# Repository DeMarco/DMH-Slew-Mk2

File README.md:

# DMH-Slew-Mk2
Second version of my Voltage Controlled Slew Limiter in Kosmo format.

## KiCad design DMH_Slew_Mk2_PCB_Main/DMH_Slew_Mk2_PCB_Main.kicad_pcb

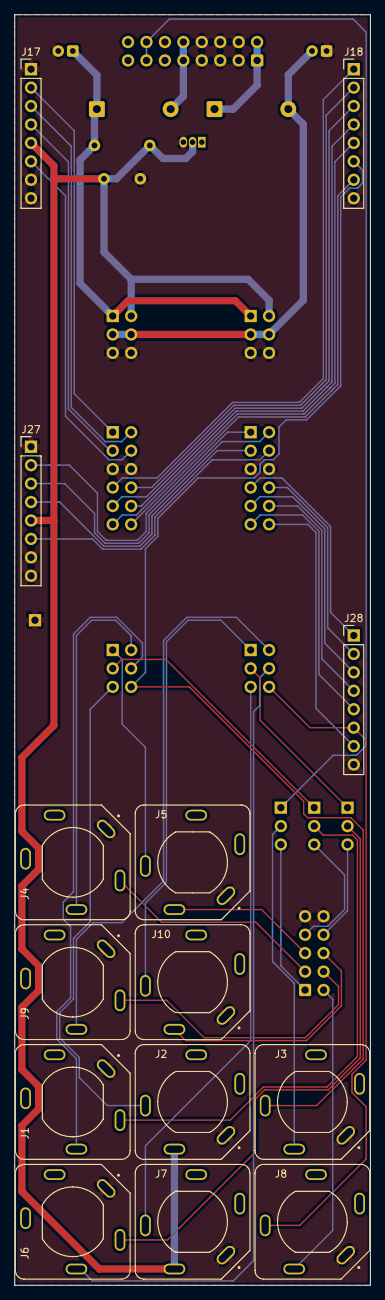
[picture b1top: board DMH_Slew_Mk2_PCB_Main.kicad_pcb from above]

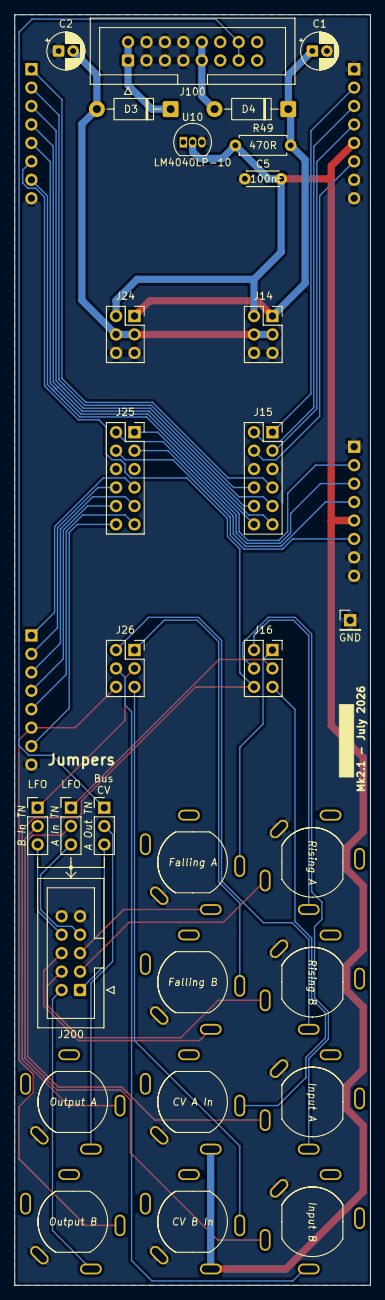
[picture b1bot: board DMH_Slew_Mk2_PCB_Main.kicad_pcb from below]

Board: 2 copper layers, 49.0 x 175.0 mm, 33 parts (19 on the bottom side), 50 nets.

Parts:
C1, C2: 47uF; CP_Radial_D5.0mm_P2.00mm
C5: 100nF; C_Disc_D4.3mm_W1.9mm_P5.00mm
D3, D4: SB140; D_DO-41_SOD81_P10.16mm_Horizontal
J0: Conn_01x01; PinHeader_1x01_P2.54mm_Vertical
J1, J2, J3, J4, J5, J6, J7, J8, J9, J10: TS_Jack_6.35mm_Sw; CUI_SJ-63083D
J14, J16, J24, J26: Conn_02x03_Top_Bottom; PinSocket_2x03_P2.54mm_Vertical
J15, J25: Conn_02x06_Top_Bottom; PinSocket_2x06_P2.54mm_Vertical
J17, J18, J27, J28: Conn_01x08; PinHeader_1x08_P2.54mm_Vertical
J100: IDC_02x08; IDC-Header_2x08_P2.54mm_Vertical_Eurorack
J200: IDC_02x05; IDC-Header_2x05_P2.54mm_Vertical_BackBone
JP1, JP2, JP3: Jumper_3_Bridged12; PinHeader_1x03_P2.54mm_Vertical
R49: 470R; R_Axial_DIN0207_L6.3mm_D2.5mm_P7.62mm_Horizontal
U10: LM4040LP-10; TO-92_Inline

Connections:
+10V: C5.1, J2.TN (2), J7.TN (2), J14.2, J17.5, J24.2, J27.5, R49.1, U10.2 (K)
+12V: C1.1, D4.1 (K), J14.1, J24.1, R49.2
-12V: C2.2, D3.2 (A), J14.3, J14.4, J24.3, J24.4
A_CV_Buff_M: J15.4, J17.6
A_CV_In_Jack_M: J2.T (3), J16.5
A_Diff_Amp_M: J15.1, J17.2
A_F_Gate_Jack_M: J5.T (3), J16.1
A_F_Gate_Jack_TN_M: J5.TN (2), J200.3
A_F_LED_M: J15.10, J18.4
A_Fall_CV_M: J15.3, J17.4
A_In_Jack_TN_M: J1.TN (2), JP2.2 (C)
A_Input_Jack_M: J1.T (3), J16.4
A_LinLog_Sw_p2_M: J15.8, J18.2
A_LinLog_Sw_p5_M: J15.7, J18.1
A_Loopback_M: J16.3, JP2.1 (A)
A_Out_Jack_M: J3.T (3), J16.6, J18.6
A_Out_Jack_TN_M: J3.TN (2), JP1.2 (C)
A_R_Gate_Jack_M: J4.T (3), J16.2
A_R_Gate_Jack_TN_M: J4.TN (2), J200.2
A_R_LED_M: J15.9, J18.3
A_Rise_CV_M: J15.2, J17.3
A_Rng_Sw_p1_M: J15.12, J18.7
A_Rng_Sw_p3_M: J15.11, J18.5
B_CV_Buff_M: J25.4, J27.6
B_CV_In_Jack_M: J7.T (3), J26.5
B_Diff_Amp_M: J25.1, J27.2
B_F_Gate_Jack_M: J10.T (3), J26.1
B_F_Gate_Jack_TN_M: J10.TN (2), J200.8
B_F_LED_M: J25.10, J28.4
B_Fall_CV_M: J25.3, J27.4
B_In_Jack_TN_M: J6.TN (2), JP3.2 (C)
B_Input_Jack_M: J6.T (3), J26.4
B_LinLog_Sw_p2_M: J25.8, J28.2
B_LinLog_Sw_p5_M: J25.7, J28.1
B_Loopback_M: J26.3, JP3.1 (A)
B_Out_Jack_M: J8.T (3), J26.6, J28.6
B_Out_Jack_TN_M: J8.TN (2), J200.6
B_R_Gate_Jack_M: J9.T (3), J26.2
B_R_Gate_Jack_TN_M: J9.TN (2), J200.7
B_R_LED_M: J25.9, J28.3
B_Rise_CV_M: J25.2, J27.3
B_Rng_Sw_p1_M: J25.12, J28.7
B_Rng_Sw_p3_M: J25.11, J28.5
Bus_CV_M: J100.7a, J100.7b, JP1.1 (A)
GND: C1.2, C2.1, C5.2, J0.1 (Pin_1_1), J1.S (1), J2.S (1), J3.S (1), J4.S (1), J5.S (1), J6.S (1), J7.S (1), J8.S (1), J9.S (1), J10.S (1), J14.5, J14.6, J15.5, J15.6, J17.1, J17.7, J17.8, J18.8, J24.5, J24.6, J25.5, J25.6, J27.1, J27.7, J27.8, J28.8, J100.2a, J100.2b, J100.3a, J100.3b, J100.4a, J100.4b, J200.5, J200.10, U10.3 (A)
unnamed: D3.1 (K), J100.1a, J100.1b
unnamed: D4.2 (A), J100.5a, J100.5b
unnamed: J200.1, JP1.3 (B)
unnamed: J200.4, JP2.3 (B)
unnamed: J200.9, JP3.3 (B)

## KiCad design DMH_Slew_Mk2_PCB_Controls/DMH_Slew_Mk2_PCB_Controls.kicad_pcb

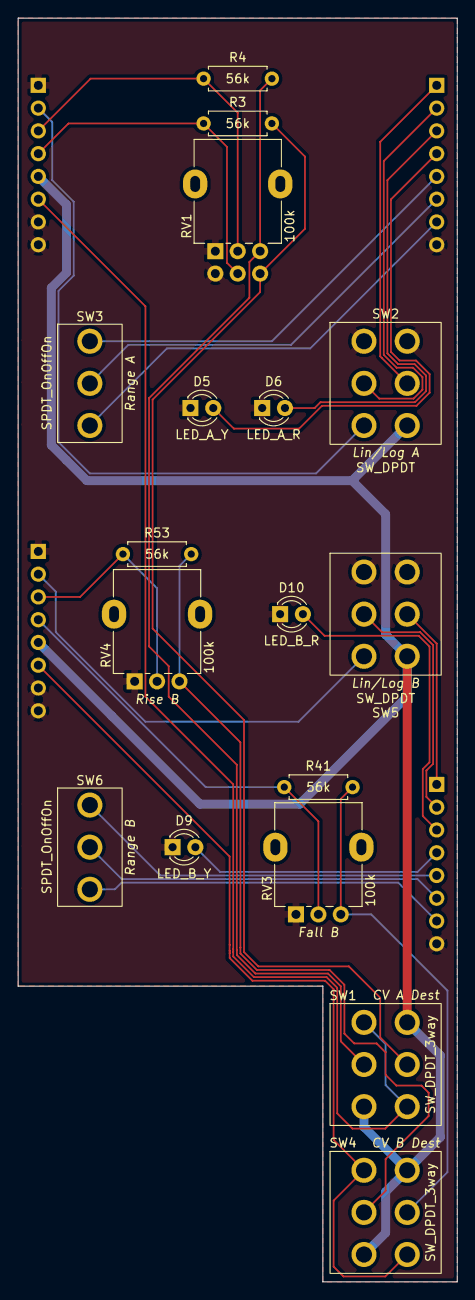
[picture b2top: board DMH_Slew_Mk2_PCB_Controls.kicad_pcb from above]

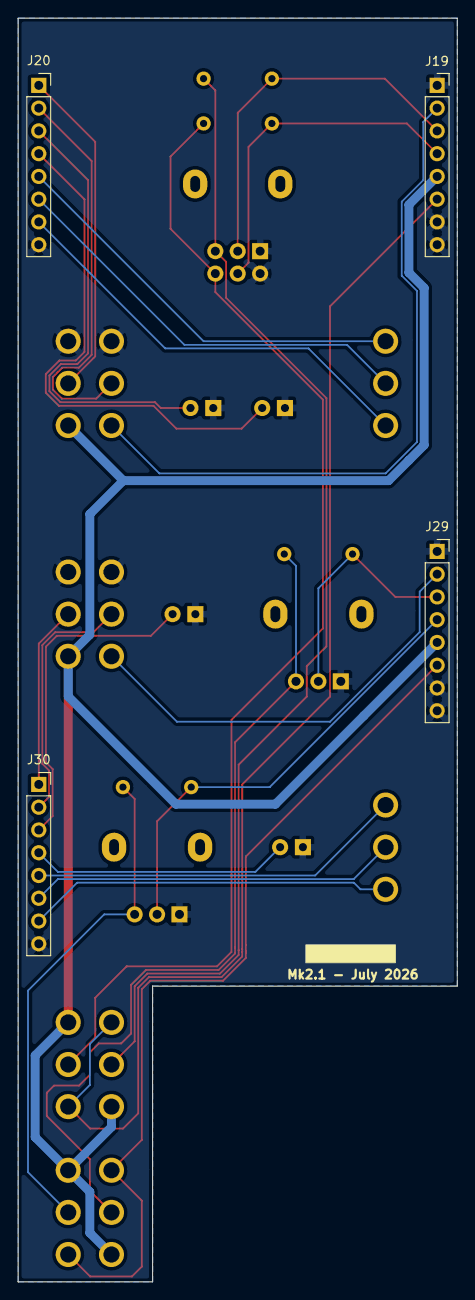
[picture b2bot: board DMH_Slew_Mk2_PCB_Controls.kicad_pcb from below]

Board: 2 copper layers, 49.0 x 141.0 mm, 21 parts (4 on the bottom side), 28 nets.

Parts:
D5: LED_A_Y; LED_D3.0mm
D6: LED_A_R; LED_D3.0mm
D9: LED_B_Y; LED_D3.0mm
D10: LED_B_R; LED_D3.0mm
J19, J20, J29, J30: Conn_01x08; PinSocket_1x08_P2.54mm_Vertical
R3, R4, R41, R53: 56k; R_Axial_DIN0207_L6.3mm_D2.5mm_P7.62mm_Horizontal
RV1: 100k; Potentiometer_Alpha_RD902F-40-00D_Dual_Vertical
RV3, RV4: 100k; Potentiometer_Alpha_RD901F-40-00D_Single_Vertical
SW1, SW4: SW_DPDT_3way; Toggle_Switch_2_Poles_TE
SW2, SW5: SW_DPDT; Toggle_Switch_2_Poles_TE
SW3, SW6: SPDT_OnOffOn; Toggle_Switch_TE

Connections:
+10V: J19.5, J29.5, SW1.1 (A), SW1.6 (C), SW2.4 (A), SW4.1 (A), SW4.6 (C), SW5.4 (A)
A_CV_Buff_C: J19.6, SW1.3 (C), SW1.4 (A)
A_Diff_Amp_C: J19.2, SW2.1 (A)
A_F_LED_C: D5.2 (A), J20.4
A_Fall_CV_C: J19.4, R3.1, RV1.5
A_LinLog_Sw_p2_C: J20.2, SW2.2 (B)
A_LinLog_Sw_p5_C: J20.1, SW2.5 (B)
A_Out_Jack_C: J20.6, SW3.2 (B)
A_R_LED_C: D6.2 (A), J20.3
A_Rise_CV_C: J19.3, R4.1, RV1.2
A_Rng_Sw_p1_C: J20.7, SW3.1 (A)
A_Rng_Sw_p3_C: J20.5, SW3.3 (C)
B_CV_Buff_C: J29.6, SW4.3 (C), SW4.4 (A)
B_Diff_Amp_C: J29.2, SW5.1 (A)
B_F_LED_C: D9.2 (A), J30.4
B_Fall_CV_C: J29.4, R41.1, RV3.2
B_LinLog_Sw_p2_C: J30.2, SW5.2 (B)
B_LinLog_Sw_p5_C: J30.1, SW5.5 (B)
B_Out_Jack_C: J30.6, SW6.2 (B)
B_R_LED_C: D10.2 (A), J30.3
B_Rise_CV_C: J29.3, R53.1, RV4.2
B_Rng_Sw_p1_C: J30.7, SW6.1 (A)
B_Rng_Sw_p3_C: J30.5, SW6.3 (C)
GND: D5.1 (K), D6.1 (K), D9.1 (K), D10.1 (K), J19.1, J19.7, J19.8, J20.8, J29.1, J29.7, J29.8, J30.8, RV1.1, RV1.4, RV3.1, RV4.1, SW2.3 (C), SW2.6 (C), SW5.3 (C), SW5.6 (C)
unnamed: R3.2, RV1.6, SW1.5 (B)
unnamed: R4.2, RV1.3, SW1.2 (B)
unnamed: R41.2, RV3.3, SW4.5 (B)
unnamed: R53.2, RV4.3, SW4.2 (B)

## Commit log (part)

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2026-04-11 Created PANEL and Main PCB projects
2026-04-11 Redesigned panel and main PCB schematic
2026-04-18 Designed Controls PCB
    ... and removed Mod feature
2026-05-15 Updated SynthStuff
2026-06-25 Generated Gerbers
